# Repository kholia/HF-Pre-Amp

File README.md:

Reference: https://www.qsl.net/py2ohh/trx/buffer/buffer.html

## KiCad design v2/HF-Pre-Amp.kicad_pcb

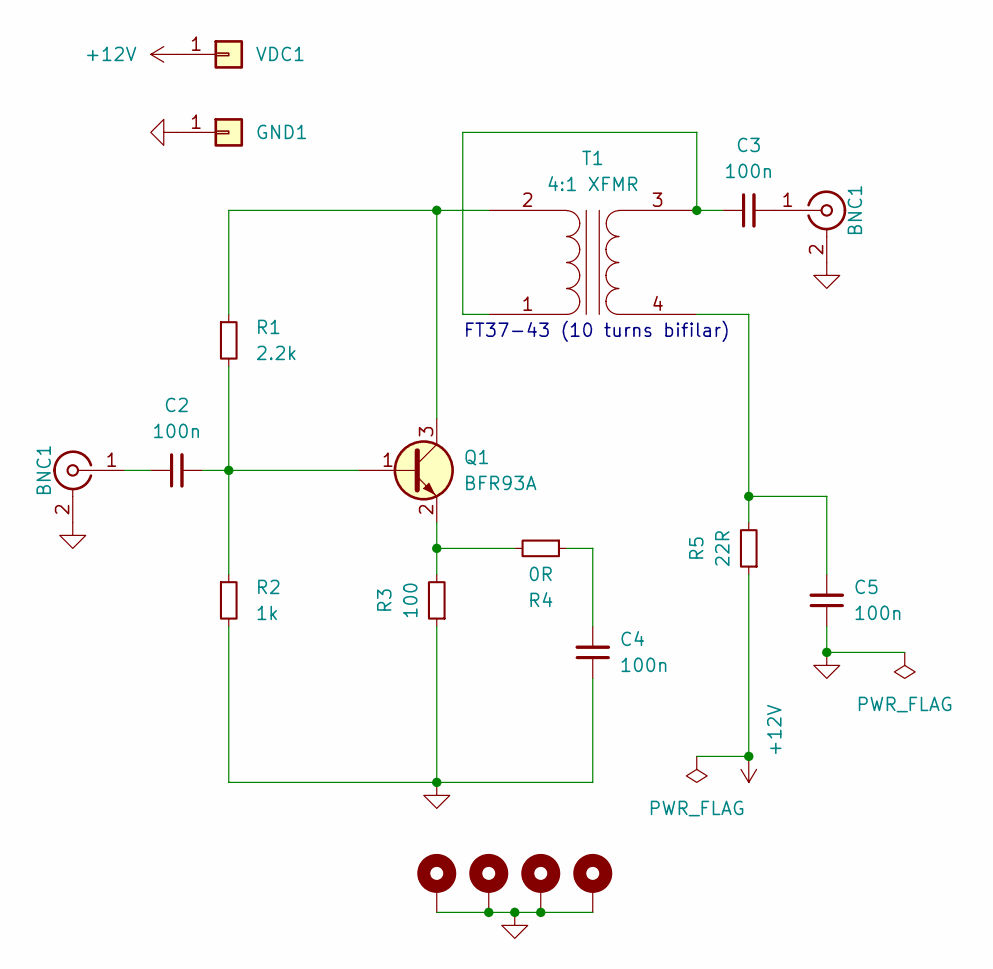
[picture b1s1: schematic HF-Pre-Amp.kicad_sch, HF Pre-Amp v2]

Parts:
BNC1: SMA; SMA_EDGELAUNCH_Modded
C2, C3, C4, C5: 100n; C_1206_3216Metric_Pad1.33x1.80mm_HandSolder
GND1: Conn_01x01; TestPoint_Pad_3.0x3.0mm
H1, H2, H3, H4: MountingHole_Pad; MountingHole_2.2mm_M2_Pad_Via
Q1: BFR93A; SOT-23_Handsoldering
R1: 2.2k; R_1206_3216Metric_Pad1.30x1.75mm_HandSolder
R2: 1k; R_1206_3216Metric_Pad1.30x1.75mm_HandSolder
R3: 100; R_1206_3216Metric_Pad1.30x1.75mm_HandSolder
R4: 0R; R_1206_3216Metric_Pad1.30x1.75mm_HandSolder
R5: 22R; R_1206_3216Metric_Pad1.30x1.75mm_HandSolder
T1: 4:1 XFMR; Transformer_Toroid_Horizontal_D10.5mm_Amidon-T37
VDC1: Conn_01x01; TestPoint_Pad_3.0x3.0mm

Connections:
+12V: R5.1, VDC1.1
GND: C4.1, C5.1, GND1.1, H1.1, H2.1, H3.1, H4.1, R2.2, R3.1; also elsewhere on the board
unnamed: C4.2, R4.1
unnamed 3: C2.1; also elsewhere on the board
unnamed 4: C3.2; also elsewhere on the board
unnamed: C2.2, Q1.1 (B), R1.2, R2.1
unnamed: Q1.3 (C), R1.1, T1.2 (AB)
unnamed: Q1.2 (E), R3.2, R4.2
unnamed: C3.1, T1.1 (AA), T1.3 (SA)
unnamed: C5.2, R5.2, T1.4 (SB)

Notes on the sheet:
FT37-43 (10 turns bifilar)

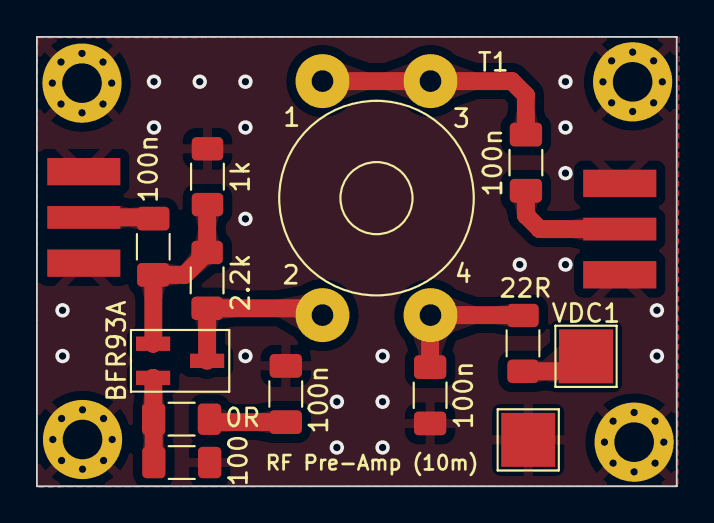
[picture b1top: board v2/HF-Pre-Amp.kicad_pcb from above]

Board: 2 copper layers, 35.5 x 25.0 mm, 19 parts (0 on the bottom side), 10 nets.

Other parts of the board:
IN1: SMA; SMA_EDGELAUNCH_Modded
OUT1: SMA; SMA_EDGELAUNCH_Modded

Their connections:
GND: IN1.2 (Ext), OUT1.2 (Ext); also elsewhere on the board
unnamed 3: IN1.1 (In); also elsewhere on the board
unnamed 4: OUT1.1 (In); also elsewhere on the board

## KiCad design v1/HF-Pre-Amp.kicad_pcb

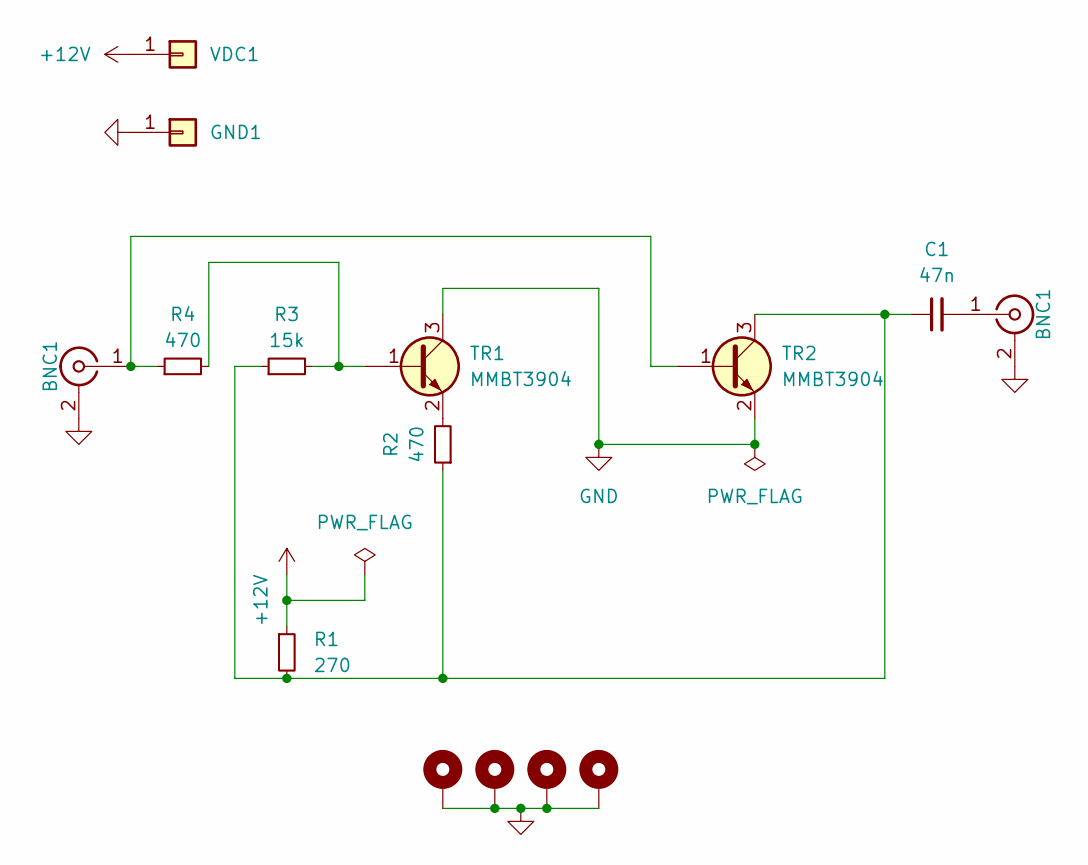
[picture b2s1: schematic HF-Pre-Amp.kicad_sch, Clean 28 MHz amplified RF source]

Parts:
BNC1: SMA; SMA_EDGELAUNCH_Modded
C1: 47n; C_1206_3216Metric_Pad1.33x1.80mm_HandSolder
GND1: Conn_01x01; TestPoint_Pad_2.5x2.5mm
H1, H2, H3, H4: MountingHole_Pad; MountingHole_2.2mm_M2_Pad_Via
R1: 270; R_1206_3216Metric_Pad1.30x1.75mm_HandSolder
R2, R4: 470; R_1206_3216Metric_Pad1.30x1.75mm_HandSolder
R3: 15k; R_1206_3216Metric_Pad1.30x1.75mm_HandSolder
TR1, TR2: MMBT3904; SOT-23_Handsoldering
VDC1: Conn_01x01; TestPoint_Pad_2.5x2.5mm

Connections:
+12V: R1.1, VDC1.1
GND: GND1.1, H1.1, H2.1, H3.1, H4.1, TR1.3 (C), TR2.2 (E); also elsewhere on the board
unnamed 2: R4.1, TR2.1 (B); also elsewhere on the board
unnamed 3: C1.2; also elsewhere on the board
unnamed: R3.2, R4.2, TR1.1 (B)
unnamed: R2.2, TR1.2 (E)
unnamed: C1.1, R1.2, R2.1, R3.1, TR2.3 (C)

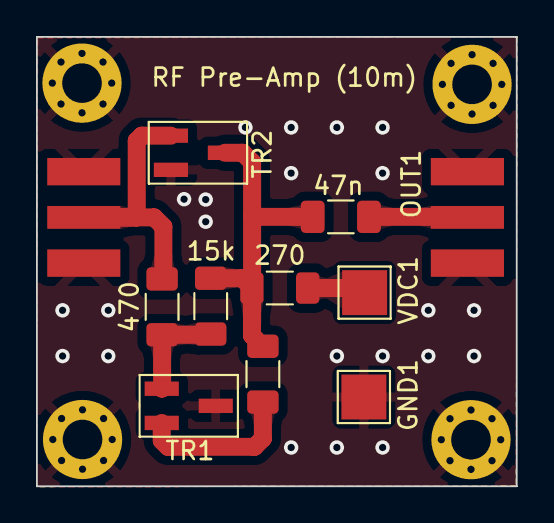
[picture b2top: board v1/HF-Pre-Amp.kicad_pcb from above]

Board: 2 copper layers, 26.7 x 25.0 mm, 15 parts (0 on the bottom side), 7 nets.

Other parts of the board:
IN1: SMA; SMA_EDGELAUNCH_Modded
OUT1: SMA; SMA_EDGELAUNCH_Modded

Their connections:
GND: IN1.2 (Ext), OUT1.2 (Ext); also elsewhere on the board
unnamed 2: IN1.1 (In); also elsewhere on the board
unnamed 3: OUT1.1 (In); also elsewhere on the board

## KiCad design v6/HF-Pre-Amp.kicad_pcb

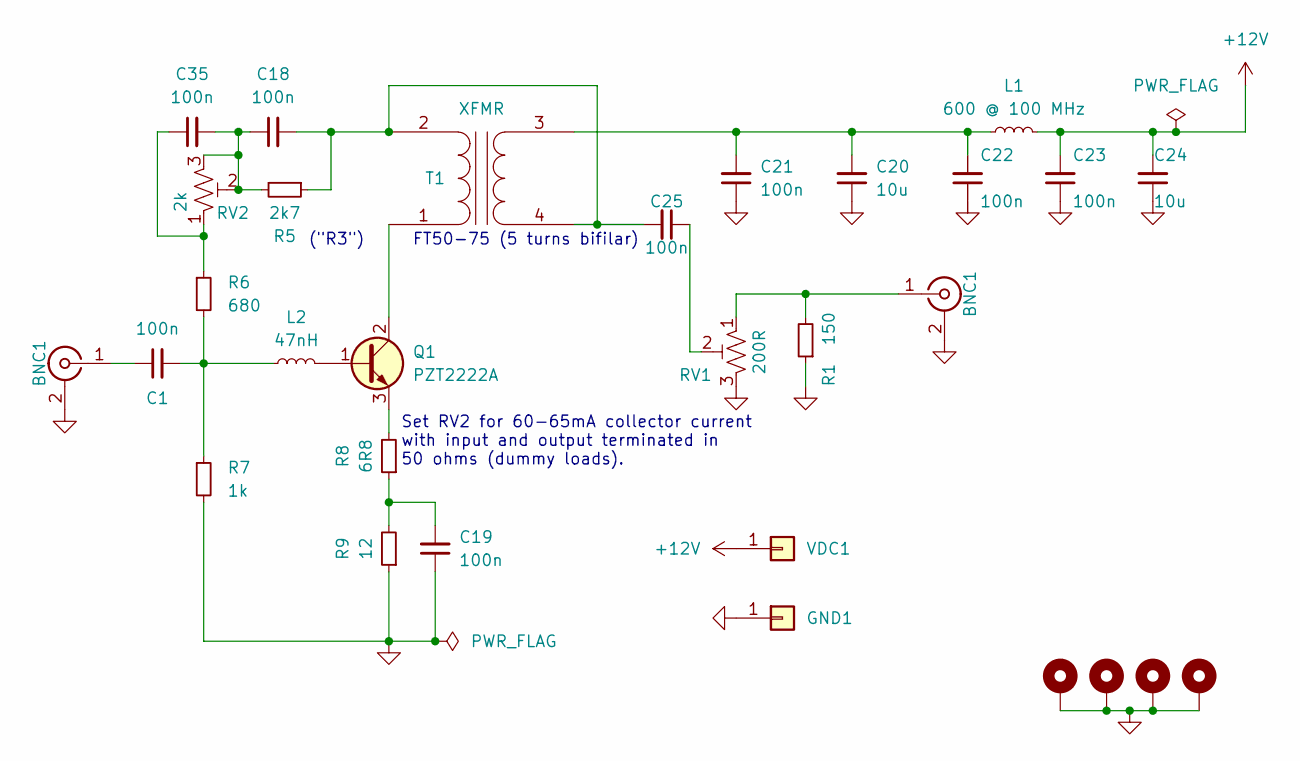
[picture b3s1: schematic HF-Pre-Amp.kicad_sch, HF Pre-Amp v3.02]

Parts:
BNC1: SMA; SMA_EDGELAUNCH_Modded
C1, C18, C19, C21, C22, C23, C25, C35: 100n; C_1206_3216Metric_Pad1.33x1.80mm_HandSolder
C20, C24: 10u; C_1206_3216Metric_Pad1.33x1.80mm_HandSolder
GND1: Conn_01x01; TestPoint_Pad_3.0x3.0mm
H1, H2, H3, H4: MountingHole_Pad; MountingHole_2.2mm_M2_Pad_Via
L1: 600 @ 100 MHz; L_1206_3216Metric_Pad1.42x1.75mm_HandSolder
L2: 47nH; L_1008_2520Metric_Pad1.43x2.20mm_HandSolder
Q1: PZT2222A; SOT-223-3_TabPin2
R1: 150; R_1206_3216Metric_Pad1.30x1.75mm_HandSolder
R5: 2k7; R_1206_3216Metric_Pad1.30x1.75mm_HandSolder
R6: 680; R_1206_3216Metric_Pad1.30x1.75mm_HandSolder
R7: 1k; R_1206_3216Metric_Pad1.30x1.75mm_HandSolder
R8: 6R8; R_1206_3216Metric_Pad1.30x1.75mm_HandSolder
R9: 12; R_1206_3216Metric_Pad1.30x1.75mm_HandSolder
RV1: 200R; Potentiometer_Bourns_3386P_Vertical
RV2: 2k; Potentiometer_Bourns_3386P_Vertical
T1: XFMR; FT50-43 Transformer
VDC1: Conn_01x01; TestPoint_Pad_3.0x3.0mm

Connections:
+12V: C23.2, C24.2, L1.2, VDC1.1
GND: C19.1, C20.1, C21.1, C22.1, C23.1, C24.1, GND1.1, H1.1, H2.1, H3.1, H4.1, R1.1, R7.2, R9.1, RV1.3; also elsewhere on the board
unnamed: C1.2, L2.1, R6.2, R7.1
unnamed: C18.1, C35.2, R5.2, RV2.2, RV2.3
unnamed: C19.2, R8.1, R9.2
unnamed: C25.1, RV1.2
unnamed: C35.1, R6.1, RV2.1
unnamed 7: C1.1; also elsewhere on the board
unnamed 8: R1.2, RV1.1; also elsewhere on the board
unnamed: L2.2, Q1.1 (B)
unnamed: Q1.2 (C), T1.1 (AA)
unnamed: Q1.3 (E), R8.2
unnamed: C18.2, C25.2, R5.1, T1.2 (AB), T1.4 (SB)
unnamed: C20.2, C21.2, C22.2, L1.1, T1.3 (SA)

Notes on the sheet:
("R3")
FT50-75 (5 turns bifilar)
Set RV2 for 60-65mA collector current with input and output terminated in 50 ohms (dummy loads).

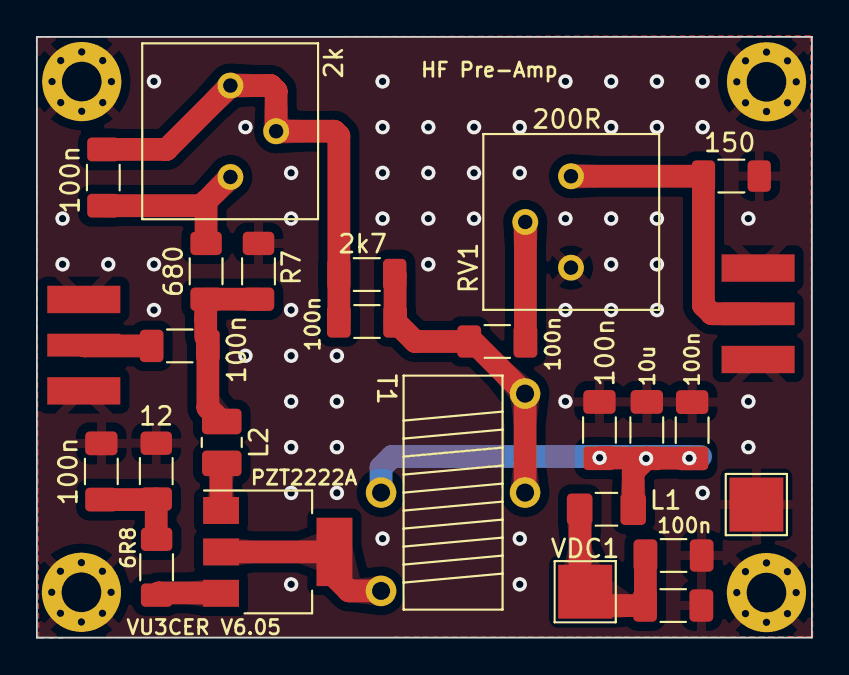
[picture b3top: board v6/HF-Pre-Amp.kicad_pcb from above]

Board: 2 copper layers, 43.1 x 33.4 mm, 30 parts (0 on the bottom side), 14 nets.

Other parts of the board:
IN1: SMA; SMA_EDGELAUNCH_Modded
OUT1: SMA; SMA_EDGELAUNCH_Modded

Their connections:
GND: IN1.2 (Ext), OUT1.2 (Ext); also elsewhere on the board
unnamed 7: IN1.1 (In); also elsewhere on the board
unnamed 8: OUT1.1 (In); also elsewhere on the board

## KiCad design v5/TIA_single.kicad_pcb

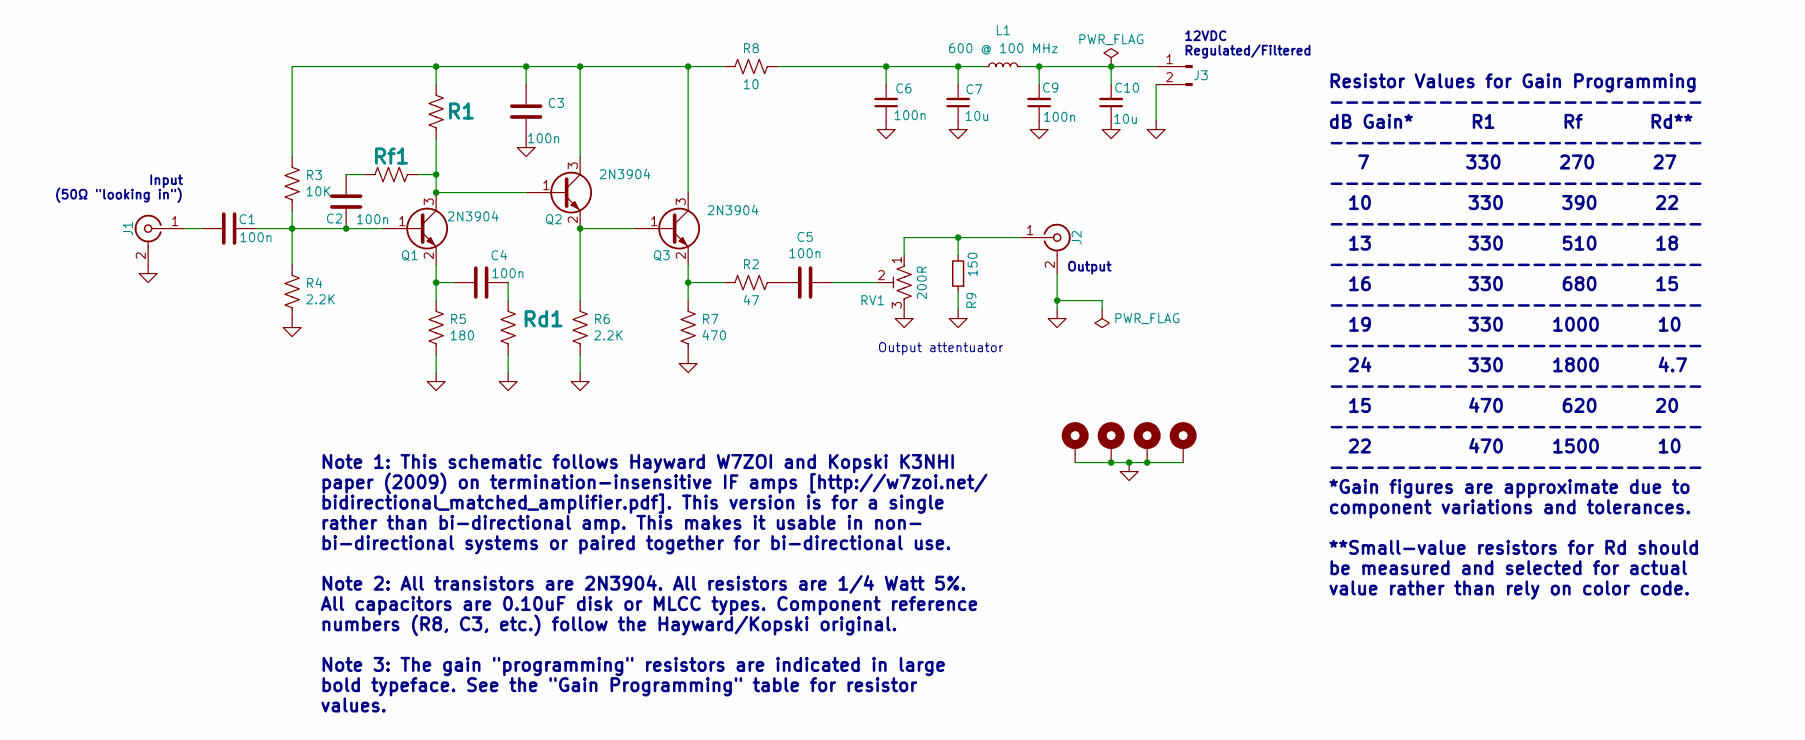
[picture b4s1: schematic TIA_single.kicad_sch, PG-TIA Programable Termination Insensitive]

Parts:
C1, C2, C3, C4, C5, C6, C9: 100n; C_1206_3216Metric_Pad1.33x1.80mm_HandSolder
C7, C10: 10u; C_1206_3216Metric_Pad1.33x1.80mm_HandSolder
H1, H2, H3, H4: MountingHole_Pad; MountingHole_2.2mm_M2_Pad_Via
J1: Conn_Coaxial; SMA_EDGELAUNCH_Modded
J2: SMA; SMA_EDGELAUNCH_Modded
J3: Conn_01x02_Male; PinHeader_1x02_P2.54mm_Vertical
L1: 600 @ 100 MHz; L_1206_3216Metric_Pad1.42x1.75mm_HandSolder
Q1, Q2, Q3: 2N3904; SOT-23_Handsoldering
R1: 330; R_1206_3216Metric_Pad1.30x1.75mm_HandSolder
R2: 47; R_1206_3216Metric_Pad1.30x1.75mm_HandSolder
R3: 10K; R_1206_3216Metric_Pad1.30x1.75mm_HandSolder
R4, R6: 2.2K; R_1206_3216Metric_Pad1.30x1.75mm_HandSolder
R5: 180; R_0805_2012Metric_Pad1.20x1.40mm_HandSolder
R7: 470; R_1206_3216Metric_Pad1.30x1.75mm_HandSolder
R8: 10; R_1206_3216Metric_Pad1.30x1.75mm_HandSolder
R9: 150; R_1206_3216Metric_Pad1.30x1.75mm_HandSolder
RV1: 200R; Potentiometer_Bourns_3296W_Vertical
Rd1: 15; R_1206_3216Metric_Pad1.30x1.75mm_HandSolder
Rf1: 680; R_1206_3216Metric_Pad1.30x1.75mm_HandSolder

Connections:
GND: C3.1, C6.1, C7.1, C9.1, C10.1, H1.1, H2.1, H3.1, H4.1, J1.2 (Ext), J2.2 (Ext), J3.2, R4.2, R5.2, R6.2, R7.2, R9.1, RV1.3, Rd1.2
unnamed: C2.2, Rf1.2
unnamed: C4.1, Rd1.1
unnamed: C5.1, RV1.2
unnamed: C5.2, R2.1
unnamed: C6.2, C7.2, L1.1, R8.1
unnamed: C1.2, J1.1 (In)
unnamed: J2.1 (In), R9.2, RV1.1
unnamed: C9.2, C10.2, J3.1, L1.2
unnamed: C1.1, C2.1, Q1.1 (B), R3.2, R4.1
unnamed: Q1.3 (C), Q2.1 (B), R1.2, Rf1.1
unnamed: C4.2, Q1.2 (E), R5.1
unnamed: C3.2, Q2.3 (C), Q3.3 (C), R1.1, R3.1, R8.2
unnamed: Q2.2 (E), Q3.1 (B), R6.1
unnamed: Q3.2 (E), R2.2, R7.1

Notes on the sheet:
Output attentuator
Note 1: This schematic follows Hayward W7ZOI and Kopski K3NHI paper (2009) on termination-insensitive IF amps [http://w7zoi.net/ bidirectional_matched_amplifier.pdf]. This version is for a single rather than bi-directional amp. This makes it usable in non- bi-directional systems or paired together 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
Output
Resistor Values for Gain Programming ------------------------ dB Gain* R1 Rf Rd** ------------------------ 7 330 270 27 ------------------------ 10 330 390 22 ------------------------ 13 330 510 18 ------------------------ 16 330 680 15 ------------------------ 19 330 1000 10 ----------------------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
Input (50Ω "looking in")
12VDC Regulated/Filtered

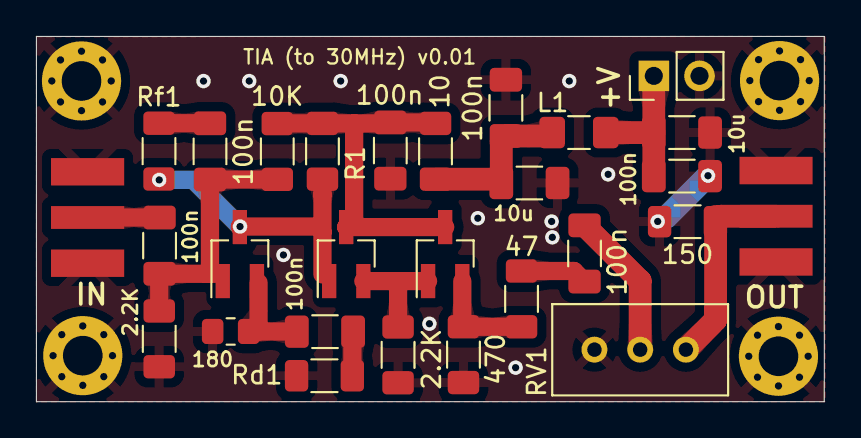
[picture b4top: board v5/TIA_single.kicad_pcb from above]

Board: 2 copper layers, 43.8 x 20.3 mm, 32 parts (0 on the bottom side), 15 nets.

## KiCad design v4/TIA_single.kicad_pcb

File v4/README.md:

# PG-TIA

Programmable-gain termination-insensitive IF amplifier.

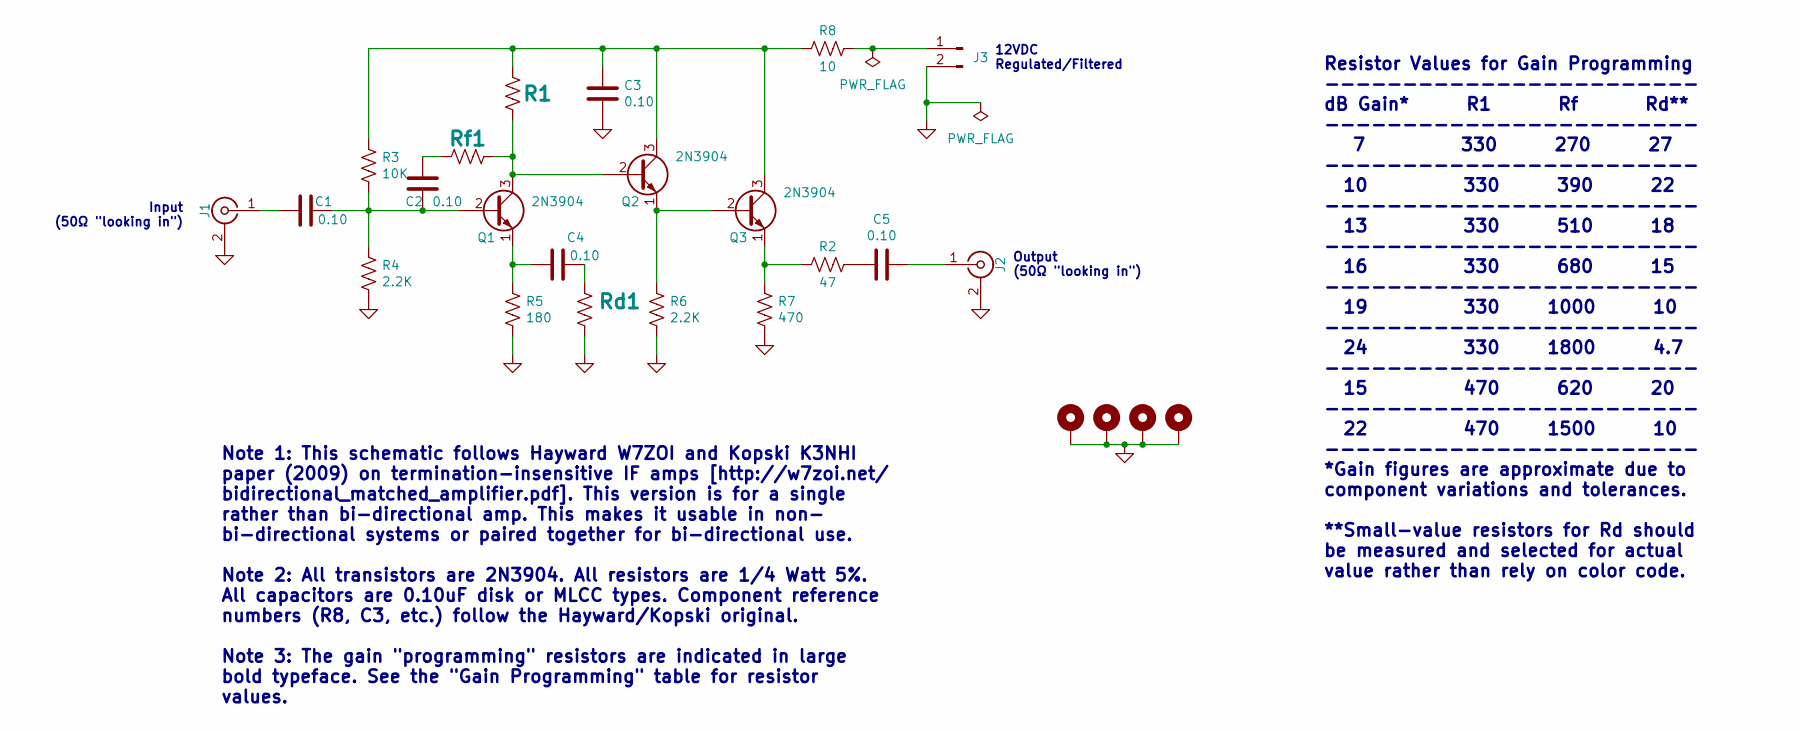
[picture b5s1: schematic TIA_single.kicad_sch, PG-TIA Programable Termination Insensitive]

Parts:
C1, C2, C3, C4, C5: 0.10; C_Disc_D3.0mm_W1.6mm_P2.50mm
H1, H2, H3, H4: MountingHole_Pad; MountingHole_2.2mm_M2_Pad_Via
J1: Conn_Coaxial; SMA_EDGELAUNCH_Modded
J2: SMA; SMA_EDGELAUNCH_Modded
J3: Conn_01x02_Male; PinHeader_1x02_P2.54mm_Vertical
Q1, Q2, Q3: 2N3904; TO-92_HandSolder
R1: 330; R_Axial_DIN0204_L3.6mm_D1.6mm_P2.54mm_Vertical
R2: 47; R_Axial_DIN0204_L3.6mm_D1.6mm_P2.54mm_Vertical
R3: 10K; R_Axial_DIN0204_L3.6mm_D1.6mm_P2.54mm_Vertical
R4, R6: 2.2K; R_Axial_DIN0204_L3.6mm_D1.6mm_P2.54mm_Vertical
R5: 180; R_Axial_DIN0204_L3.6mm_D1.6mm_P2.54mm_Vertical
R7: 470; R_Axial_DIN0204_L3.6mm_D1.6mm_P2.54mm_Vertical
R8: 10; R_Axial_DIN0204_L3.6mm_D1.6mm_P2.54mm_Vertical
Rd1: 15; R_Axial_DIN0204_L3.6mm_D1.6mm_P2.54mm_Vertical
Rf1: 680; R_Axial_DIN0204_L3.6mm_D1.6mm_P2.54mm_Vertical

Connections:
GND: C3.1, H1.1, H2.1, H3.1, H4.1, J1.2 (Ext), J2.2 (Ext), J3.2, R4.2, R5.2, R6.2, R7.2, Rd1.2
unnamed: C2.2, Rf1.2
unnamed: C4.1, Rd1.1
unnamed: C5.2, R2.1
unnamed: C1.2, J1.1 (In)
unnamed: C5.1, J2.1 (In)
unnamed: J3.1, R8.1
unnamed: C1.1, C2.1, Q1.2 (B), R3.2, R4.1
unnamed: Q1.3 (C), Q2.2 (B), R1.2, Rf1.1
unnamed: C4.2, Q1.1 (E), R5.1
unnamed: C3.2, Q2.3 (C), Q3.3 (C), R1.1, R3.1, R8.2
unnamed: Q2.1 (E), Q3.2 (B), R6.1
unnamed: Q3.1 (E), R2.2, R7.1

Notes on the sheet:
Note 1: This schematic follows Hayward W7ZOI and Kopski K3NHI paper (2009) on termination-insensitive IF amps [http://w7zoi.net/ bidirectional_matched_amplifier.pdf]. This version is for a single rather than bi-directional amp. This makes it usable in non- bi-directional systems or paired together 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
Output (50Ω "looking in")
Resistor Values for Gain Programming ------------------------ dB Gain* R1 Rf Rd** ------------------------ 7 330 270 27 ------------------------ 10 330 390 22 ------------------------ 13 330 510 18 ------------------------ 16 330 680 15 ------------------------ 19 330 1000 10 ----------------------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
Input (50Ω "looking in")
12VDC Regulated/Filtered

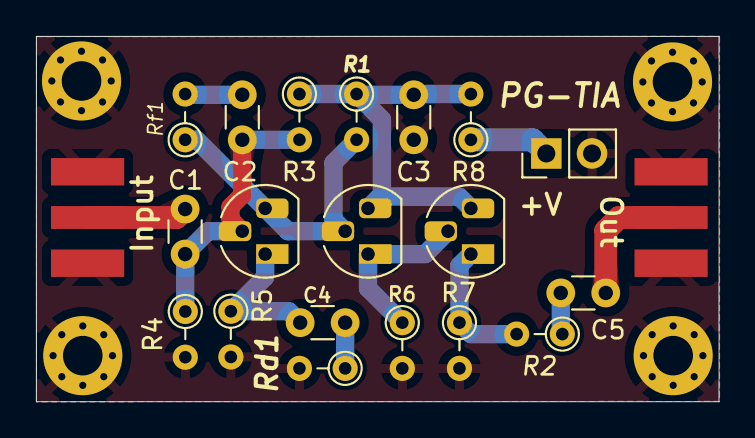
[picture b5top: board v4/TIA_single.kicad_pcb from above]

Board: 2 copper layers, 37.9 x 20.3 mm, 25 parts (0 on the bottom side), 13 nets.
